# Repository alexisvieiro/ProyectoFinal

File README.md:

# Proyecto Final
  -Hardware y Software para un Hub de SNMP con sensores de temperatura y apertura de puertas, 
  realizado en Kicad y Visual Studio Code.
  
  -APP en android para la visualización de gráficas tomadas de la API de Zabbix.

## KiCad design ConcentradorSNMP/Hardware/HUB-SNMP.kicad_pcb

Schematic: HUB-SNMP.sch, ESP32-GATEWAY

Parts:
C1: 10uF/6.3V/20%/X5R/C0805/1mΩ; C_0805_5MIL_DWS
C2, C8, C9, C12: 22uF/6.3V/20%/X5R/C0603; C_0603_5MIL_DWS
C3, C4: 4.7uF/6.3V/20%/X5R/C0805/1mΩ; C_0805_5MIL_DWS
C5: 10uF/6.3V/20%/X5R/C0805/1mΩ; C_0805_2012Metric_Pad1.18x1.45mm_HandSolder
C11, C13, C14, C15, C17: 100nF/50V/20%/Y5V/C0603; C_0603_5MIL_DWS
C16: 2.2uF/6.3V/10%/X5R/C0603; C_0603_5MIL_DWS
C18: NA(10uF/6.3V/20%/X5R/C0603); C_0603_5MIL_DWS
C19: 1nF/2000V/10%/X7R/C1206; C_1206_5MIL_DWS_ISO
C20: NA(1nF/2000V/10%/X7R/C1206); C_1206_5MIL_DWS_ISO
DOOR1, DOOR2, DOOR3, DOOR4: Conn_01x02; Molex_KK-254_AE-6410-02A_1x02_P2.54mm_Vertical
FET1: WPM2015-3/TR; SOT23
FID2, FID3: Fiducial; Fiducial1x3
GND1: TESTPAD; TESTPAD_40-ROUND
J1: Conn_01x07_Male; PinHeader_1x07_P2.54mm_Vertical
L1: NA(FB0805/600R/2A); L_0805_5MIL_DWS
L2: 2.2uH/9A/DCR=35mR/20%/3.00x3.00x1.50mm/CD32(NR301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; SMD_0530
L3: FB0805/600R/2A; L_0805_5MIL_DWS
LAN1: RJLD-060TC1(LPJ4013EDNL); RJLBC-060TC1
MH1, MH2: Mounting_hole_Shield_3.3mm
PHY_RST1: Opened; SJ
R3: 2.2k/R0603; R_0603_5MIL_DWS
R5: 1k/R0603; R_0603_5MIL_DWS
R6, R29, R38: 10k/R0603; R_0603_5MIL_DWS
R19: 442k/1%/50mW/R0603; R_0603_5MIL_DWS
R20: 100k/1%/63mw/R0603; R_0603_5MIL_DWS
R24: 1M/R0603; R_0603_5MIL_DWS
R25: 0R(Board_Mounted); R_0603_5MIL_DWS
R26, R27: 330R/R0603; R_0603_5MIL_DWS
R28, R31, R32, R33: 49.9R/1%/R0603; R_0603_5MIL_DWS
R35: 4.7K/R0603; R_0603_1608Metric_Pad0.98x0.95mm_HandSolder
R36, R40, R41, R42: 440/R0603; R_0603_1608Metric_Pad0.98x0.95mm_HandSolder
R39: 12.1k/1%/R0603; R_0603_5MIL_DWS
R54: 10K/R0603; R_0603_5MIL_DWS
RESET1: TAC-SWITCH SMD 6X6MM; SW_SPST_PTS645
RM2, RM3: RA1206_(4X0603)_4B8_2.2k; R_MATRIX_4
T1: DTC114YKA; SOT23
TEMP1: Conn_01x03; Molex_KK-254_AE-6410-03A_1x03_P2.54mm_Vertical
U1, U5, U6, U7: ACPL-217-56AE; SO-4_4.4x2.3mm_P1.27mm
U2: TLV62569DBVT(SOT23-5); SOT-23-5
U3: ESP32-WROOM-32D-4MB; ESP-WROOM-32_MODULE
U4: LAN8710A-EZC(QFN32); QFN32_EP(33)_5.00x5.00x0.90mm_Pitch_0.50mm
USB-UART2: USB_B_Micro; USB_Micro-B_Amphenol_10104110_Horizontal

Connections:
+3.3VLAN: C8.1, C9.1, C13.1, FET1.3, L1.2, L3.1, R38.2, RM2.3.1, RM2.4.1, RM3.1.2, RM3.2.2, RM3.3.2, U4.12 (VDDIO)
+3V3: C1.1, C2.1, C5.1, FET1.2, J1.2, L1.1, L2.2, R6.1, R19.2, R24.1, R29.1, R35.2, R36.2, R40.2, R41.2, R42.2, R54.2, TEMP1.2, U3.2 (3V3)
+5V: C3.1, C4.1, U2.1 (EN), U2.4 (IN), USB-UART2.1 (VBUS)
/ESP_EN: J1.3, R24.2, RESET1.2, U3.3 (EN)
/GPI34: U3.6 (GPI34/ADC1_CH6/RTC_GPIO4)
/GPI35: U3.7 (GPI35/ADC1_CH7/RTC_GPIO5)
/GPI36: U3.4 (GPI36/SENSOR_VP/ADC_H/ADC1_CH0/RTC_GPIO0)
/GPI39: U3.5 (GPI39/SENSOR_VN/ADC1_CH3/ADC_H/RTC_GPIO3)
/GPIO0: J1.7, R54.1, U3.25 (GPIO0/ADC2_CH1/TOUCH1/RTC_GPIO11/CLK_OU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)
/GPIO1\U0TXD: J1.4, U3.35 (GPIO1/U0TXD/CLK_OUT3/EMAC_RXD2)
/GPIO2\HS2_DATA0: R3.2, U3.24 (GPIO2/ADC2_CH2/TOUCH2/RTC_GPIO12/HSPIWP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)
/GPIO3\U0RXD: J1.5, U3.34 (GPIO3/U0RXD/CLK_OUT2)
/GPIO4\HS2_DATA1: J1.6, U3.26 (GPIO4/ADC2_CH0/TOUCH0/RTC_GPIO10/HSPIHD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)
/GPIO5\PHY_PWR: T1.1 (B), U3.29 (GPIO5/VSPICS0/HS1_DATA6/EMAC_RX_CLK)
/GPIO12\HS2_DATA2: U3.14 (GPIO12/ADC2_CH5/TOUCH5/RTC_GPIO15/MTDI/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)
/GPIO13\TEMP1: R35.1, TEMP1.3, U3.16 (GPIO13/ADC2_CH4/TOUCH4/RTC_GPIO14/MTCK/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)
/GPIO14\DOOR3: U3.13 (GPIO14/ADC2_CH6/TOUCH6/RTC_GPIO16/MTMS/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), U6.4
/GPIO15\HS2_CMD: R29.2, U3.23 (GPIO15/ADC2_CH3/TOUCH3/MTDO/HSPICS0/RTC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)
/GPIO16\DOOR4: U3.27 (GPIO16/HS1_DATA4/U2RXD/EMAC_CLK_OUT), U7.4
/GPIO17\EMAC_CLK_OUT_180: U3.28 (GPIO17/HS1_DATA5/U2TXD/EMAC_CLK_OUT_180), U4.5 (XTAL1/CLKIN)
/GPIO18\MDIO(RMII): RM3.1.1, U3.30 (GPIO18/VSPICLK/HS1_DATA7), U4.16 (MDIO)
/GPIO19\EMAC_TXD0(RMII): U3.31 (GPIO19/VSPIQ/U0CTS/EMAC_TXD0), U4.22 (TXD0)
/GPIO21\EMAC_TX_EN(RMII): U3.33 (GPIO21/VSPIHD/EMAC_TX_EN), U4.21 (TXEN)
/GPIO22\EMAC_TXD1(RMII): U3.36 (GPIO22/VSPIWP/U0RTS/EMAC_TXD1), U4.23 (TXD1)
/GPIO23\MDC(RMII): U3.37 (GPIO23/VSPID/HS1_STROBE), U4.17 (MDC)
/GPIO25\EMAC_RXD0(RMII): RM3.3.1, U3.10 (GPIO25/DAC_1/ADC2_CH8/RTC_GPIO6/EMAC_RX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), U4.11 (RXD0/MODE0)
/GPIO26\EMAC_RXD1(RMII): RM2.4.2, U3.11 (GPIO26/DAC_2/ADC2_CH9/RTC_GPIO7/EMAC_RX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), U4.10 (RXD1/MODE1)
/GPIO27\EMAC_RX_CRS_DV: RM3.2.1, U3.12 (GPIO27/ADC2_CH7/TOUCH7/RTC_GPIO17/EMAC_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), U4.15 (COL/CRS_DV/MODE2)
/GPIO32\PUERTA1: U1.4, U3.8 (GPIO32/XTAL_32K_P/ADC1_CH4/TOUCH9/RTC_G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)
/GPIO33\PUERTA2: U3.9 (GPIO33/XTAL_32K_N/ADC1_CH5/TOUCH8/RTC_G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), U5.4
/PHYAD0: RM3.4.1, U4.13 (RXER/RXD4/PHYAD0)
/PHYAD1: RM2.1.2, U4.7 (RXCLK/PHYAD1)
/PHYAD2: RM2.2.2, U4.8 (RXD3/PHYAD2)
/RMIISEL: RM2.3.2, U4.9 (RXD2/RMIISEL)
/VDD1A-2A: C11.1, C12.1, C14.1, C15.1, L3.2, LAN1.3 (COM), LAN1.6 (NC), R25.1, R25.2, R26.1, R28.1, R31.1, R32.1, R33.1, U4.1 (VDD2A), U4.27 (VDD1A)
/VDDCR: C16.1, C17.1, U4.6 (VDDCR)
GND: C1.2, C3.2, C4.2, C5.2, C8.2, C9.2, C11.2, C12.2, C13.2, C14.2, C15.2, C16.2, C17.2, C18.1, C19.2, C20.2, DOOR1.1, DOOR2.1, DOOR3.1, DOOR4.1, GND1.1, J1.1, MH1.GND1, MH2.GND1, PHY_RST1.1, R3.1, R20.2, R27.2, R39.2, RESET1.1, RM2.1.1, RM2.2.1, RM3.4.2, T1.2 (E), TEMP1.1, U1.3, U2.2 (GND), U3.1 (GND), U3.15 (GND), U3.38 (GND), U3.39 (THERMAL_PAD), U4.24 (TXD2), U4.25 (TXD3), U4.33 (GND), U5.3, U6.3, U7.3, USB-UART2.5 (GND), USB-UART2.6 (Shield)
unnamed: C2.2, FET1.1, R5.1, R6.2
unnamed: C18.2, PHY_RST1.2, R38.1, U4.19 (NRST)
unnamed: C19.1, C20.1, LAN1.GND1, LAN1.GND2
unnamed: DOOR1.2, U1.2
unnamed: DOOR2.2, U5.2
unnamed: DOOR3.2, U6.2
unnamed: DOOR4.2, U7.2
unnamed: L2.1, U2.3 (LX)
unnamed: LAN1.1 (TD+), R33.2, U4.29 (TXP)
unnamed: LAN1.2 (TD-), R32.2, U4.28 (TXN)
unnamed: LAN1.7 (RD+), R31.2, U4.31 (RXP)
unnamed: LAN1.8 (RD-), R28.2, U4.30 (RXN)
unnamed: LAN1.AG1 (AG), R26.2
unnamed: LAN1.AY1 (AY), U4.3 (LED1/REGOFF)
unnamed: LAN1.KG1 (KG), U4.2 (LED2/NINTSEL)
unnamed: LAN1.KY1 (KY), R27.1
unnamed: R5.2, T1.3 (C)
unnamed: R19.1, R20.1, U2.5 (FB)
unnamed: R36.1, U6.1
unnamed: R39.1, U4.32 (RBIAS)
unnamed: R40.1, U1.1
unnamed: R41.1, U5.1
unnamed: R42.1, U7.1

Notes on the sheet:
Vout=0.6*(1+Ra/Rb)
Fuente de Alimentación
In RMII Mode
Ethernet
ESP-WROOM-32 MODULO
Bootstrapping Pins Settings
Voltage of Internal LDO(VDD_SDIO)
Pin
Default
3.3V
1.8V
Booting Mode
GPIO12/MTDI
Pull-Down
GPIO0
GPIO2
Pull-Up
SPI Flash Boot
Download Boot
Don't-care
Debugging Log on U0TXD During Booting
U0TXD Toggling
U0TXD Silent
GPIO15/MTDO
Timing of SDIO Slave
Falling-edge:Output
Falling-edge:Input
Rising-edge:Output
Rising-edge:Input
GPIO5\PHY_PWR
Sensores
The PHY is setted up as follows: MODE: All capable(10/100Base) -Auto-negotiation enabled -RMII Configuration -SMI address: 0x00
Programador
Mounting Holes
Fiduciales
(logs)
GPIO5\PHY_PWR:
MTDO/GPIO15:
GPIO4:
GPIO2:

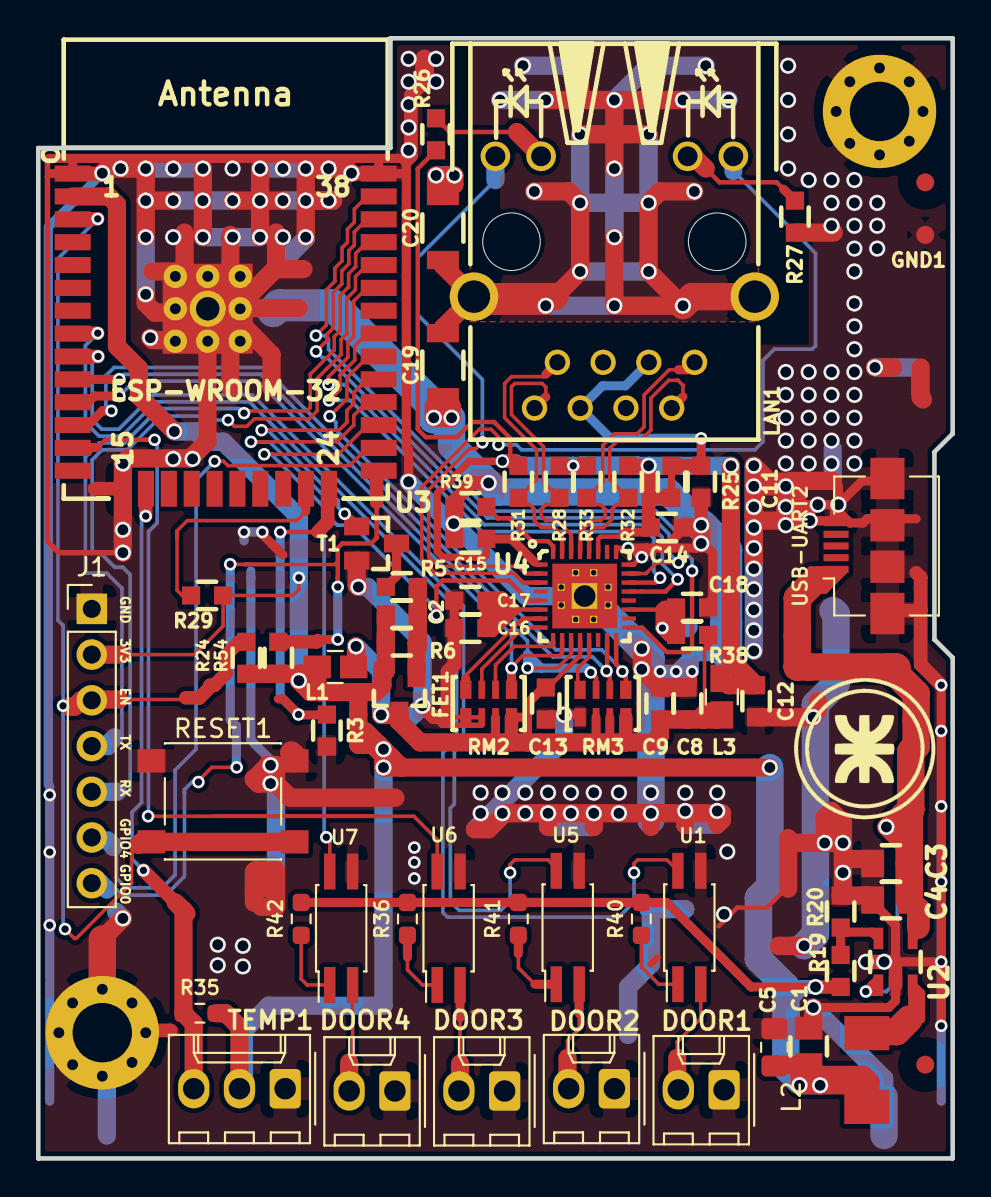
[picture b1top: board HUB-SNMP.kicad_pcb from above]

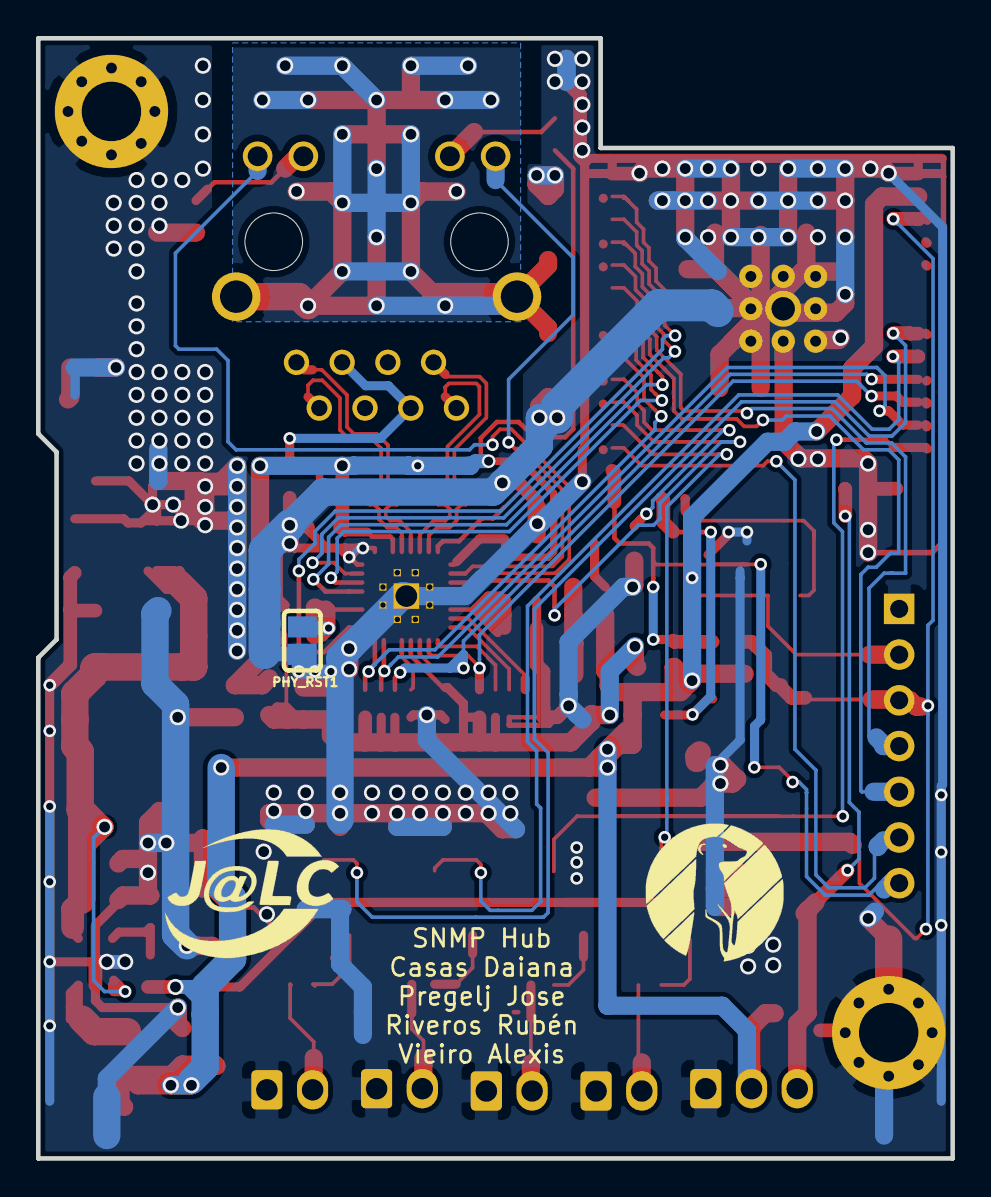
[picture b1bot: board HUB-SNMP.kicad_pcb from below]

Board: 2 copper layers, 50.8 x 62.2 mm, 70 parts (3 on the bottom side), 55 nets.

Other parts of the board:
G2: LOGO JLCPCB; jlcpcb_logo
G3: LOGO ERICNET; ericnet_logo

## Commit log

2021-07-10 Commit inicial
2021-07-10 Ahora la temperatura es redondeada al entero mas cercano, en vez del entero menor.
2021-07-16 Create farfield_12g.ffs
    Esto es una prueba
2021-07-16 Delete farfield_12g.ffs
    Vuelta para atrás
2021-08-13 mib2zabbix actualizado
    Se actualizó mib2zabbix para evitar problemas con la key en los traps generados.
2021-08-13 MIBS de Fortigate agregados de nuevo
2021-08-16 Archivos de placa actualizados.
    Se eliminaron archivos innecesarios de software y archivos de kicad actualizados.
2021-08-17 Proyecto de kicad actualizado.
    Se eliminó completamente la sección de la MicroSD
2021-08-18 Proyecto de kicad actualizado
    Se retiró la parte del programador USB y otras menores asociadas a esta.
2021-08-21 Proyecto de Kicad actualizado
    Fuente corregida. Programador agregado. Cambios menores.
2021-08-22 Proyecto de kicad actualizado.
    Se agregaron los conectores adecuados y se rutearon los gpio para estos. Queda pendiente ubicarlos correctamente para evitar el solapamiento de estos. Se acomodaron algunas resistencias y se eliminar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
2021-08-23 Proyecto en kicad actualizado
    Se modificó la posición de la pinera para programar la placa. Recolocaron los conectores de los sensores y se agregaron sus resistencias mas el modelo 3D de todo esto.
2021-08-24 Proyecto en kicad actualizado
    Push button agregado, se acomodaron los sensores y se agregó un capacitor a la salida de la fuente
2021-08-25 Proyecto en kicad actualizado
    Se agregaron logos propios. Y se corrigieron otras serigrafias.
2021-08-27 Carga de la app
2021-08-27 Prueba piloto
2021-08-27 Carga de la app android
2021-08-27 Placa kicad actualizada
2021-08-27 Placa de kicad actualizada
    Se agregaron los optoacopladores en los sensores de puerta, y se movieron los logos en la silkscreen de Ericnet y JLCPCB para la capa de atrás.
2021-08-27 Proyecto en kicad actualizado
    Se modificó el footprint del Inductor de la fuente
2021-08-27 Proyecto en kicad actualizado
    Esquemático actualizado
2021-08-28 Se agregaron 2 sensores de puerta y se sacó uno de temperatura
2021-09-01 codigo de esp32 se le agrego el oid de freeheap
2021-09-04 Codigo de ESP32 actualizado
2021-09-10 Gerbers + ESP32 https server
    Se agregaron gerbers y cambios finales de la placa. Se agrego un servidor https al codigo para el esp32
2021-10-01 ultima version?
    ultima versión app pepe
2021-10-09 Agregado del menú de items al dashboard
2021-10-13 Uso de nueva librería de gráficas
2021-10-17 cambios del servidot https
2021-10-17 Ahora cambia entre dhcp y ipfja directamente del webserver
2021-10-20 Cambios en el servidor
2021-10-21 Cambios Server
2021-10-21 Cambios en el server. Muestra correctamente la IP actualmente configurada
2021-10-22 Agrego de ventanas de tiempo
2021-10-22 Agregado proyecto en vscode
2021-10-27 Cambio de card en el menú de hosts
2021-10-27 Cambios en el https server para configurar la ip del hub snmp
2021-10-31 Finalizado webserver
2021-10-31 Eliminado proyecto en arduino
2021-10-31 Reordenado carpetas de esp32 hub
2021-10-31 Se movio lac arpeta .vscode al lugar correcto
2021-11-05 Agregado de lista completa de hosts y items respectivos
2021-11-17 Respuestas del ESP32 a oids estandar actualizado. Se agregaron oids para la consulta del estado de las puertas.
2021-11-19 App para notificiaciones modelo agregada
2021-11-19 Cambios menores en onMessageReceived
2021-11-21 Proyecto de PCB en Kicad actualizados
    -Se modifico el nombre del proyecto en kicad.
    -Se generó el BOM actualizado.
    -Se generó el pdf del esquematico actualizado.
    -Se eliminaron archivos viejos innecesarios
2021-11-21 Nombres de archivos de esquematico y bom actualizados.
2021-11-24 Finalizada la búsqueda de hosts
2021-12-03 Agregada la muestra de problemas y las notificaciones
2021-12-04 version con notificaciones
2021-12-08 Cambios en interfaz gráfica V1
2021-12-10 Arreglos varios
2021-12-12 retoques estéticos
2021-12-14 cambios de pines en los sensores de puerta
2021-12-14 Versión final
2021-12-14 traducido "no data" en app
2021-12-15 Carcasa stl actualizada
2022-01-04 Se borraron archivos innecesarios
2022-03-19 Cambios SNMP
2022-03-19 Layouts Subidos
2022-03-19 Subido test de aceptación
2022-03-20 Versión final de la app
2022-03-20 Tesina y Poster subidos
2022-03-20 Nombres de los Informes cambiados
2022-03-22 Cambio nombres de carpetas
2022-03-22 cambio carpetas
2022-03-22 cambio carpetas 2
2023-11-21 notificaciones.py creada
    se agrego script para mandar notificaciones de android via zabbix
2024-01-09 Cambios en libreria Ethernet y Template ESP32 SNMP Agregado
2024-02-07 Actualizado tesina
2024-02-12 eliminacion de comentarios
2024-02-12 Tesina actualizada
2024-02-15 tesina actualizada - proyecto kicad actualizado
